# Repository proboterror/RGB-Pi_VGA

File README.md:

# RGB-Pi with VGA 15 kHz

Improved [RGB-Pi adapter](https://www.rgb-pi.com) for use with RGB-Pi OS.

Based on [open schematic published by mortaca](https://github.com/mortaca/RGB-Pi).

Original RGB-Pi documentation: [www.mortaca.com/docs/wiki](https://www.mortaca.com/docs/wiki/index.php?title=RGB-Pi)

Changes:
- Added VGA (DSUB-15) 15 kHz connector (Warning: 31 kHz VGA monitors not supported). 
- Proper sync combiner, borrowed from from [BKM-129X clone board](https://github.com/skumlos/bkm-129x-scart-vga), see also [KabukiFlux's RGBpi cable sync mixer](https://github.com/KabukiFlux/pi-rgb-cable-sync-mixer).
- Improved R-2R RGB DAC.
- PWM audio buffered with [SN74LVC2G34 Dual Buffer Gate](<datasheets/SN74LVC2G34 Dual Buffer Gate.pdf>) powered from [PS7A2033 Ultra-Low-Noise LDO](<datasheets/TPS7A20 300-mA, Ultra-Low-Noise, Low-IQ, High PSRR LDO.pdf>), with separate analog ground, in order to reduce Raspberry Pi internal power noise.
- Added 3.5 mm audio jack connector.

## Schematics:<br>

## Board view:<br>

## Bill of Materials
|Reference|Value|Footprint|Qty|
|-----|-----|-----|-----|
|C1,C2|100nF|0805|2|
|C8,C9|10uF|0805|2|
|U2|SN74LVC2G34DBVR|SOT-23-6|1|
|U3|TPS7A2033PDBVR|SOT-23-5|1|
|F1|MF-NSMF012-2| 1206 Bourns MF-NSMF012-2 0.12A 30V|1|
|J1|Raspberry_Pi_4| PinHeader_2x20_P2.54mm_Vertical |1|
|J2|SCART-F|CS-102 (SCART-21S)|1|
|J3|DE15 Socket / DSUB-15-HD / VGA| DSUB-15-HD_Socket_Horizontal P2.29x1.90mm EdgePinOffset3.03mm MountingHolesOffset4.94mm|1|
|J4|SJ1-3535NG|CUI/Same Sky Device SJ1-3535NG|1|
|Q1|MMBT3904|SOT-23|1|
|R1|120R|0805|1|
|R2,R3|1K|0805|2|
|R6|100R|0805|1|
|R7|10K|0805|1|
|R8|1K|0805|1|
|R9|470R|0805|1|
|RN1,RN2,RN5,RN8|R = 240R or 300R 1%|Resistor Array 4x0603 |4|
|RN3,RN4,RN6,RN7,RN9,RN10|2R = 475R or 604R 1%|Resistor Array 4x0603|6|

Optional (SCART 5V->12V Converter for Status & Aspect Ratio switch):

|Reference|Value|Footprint|Qty|
|-----|-----|-----|-----|
|C5|100nF|0805|1|
|C3,C4|220nF|0805|2|
|C6,C7|4.7uF|Tantalum EIA-3528-21 / Kemet-B|2|
|U1|ST662A|SO-8_3.9x4.9mm_P1.27mm|1|

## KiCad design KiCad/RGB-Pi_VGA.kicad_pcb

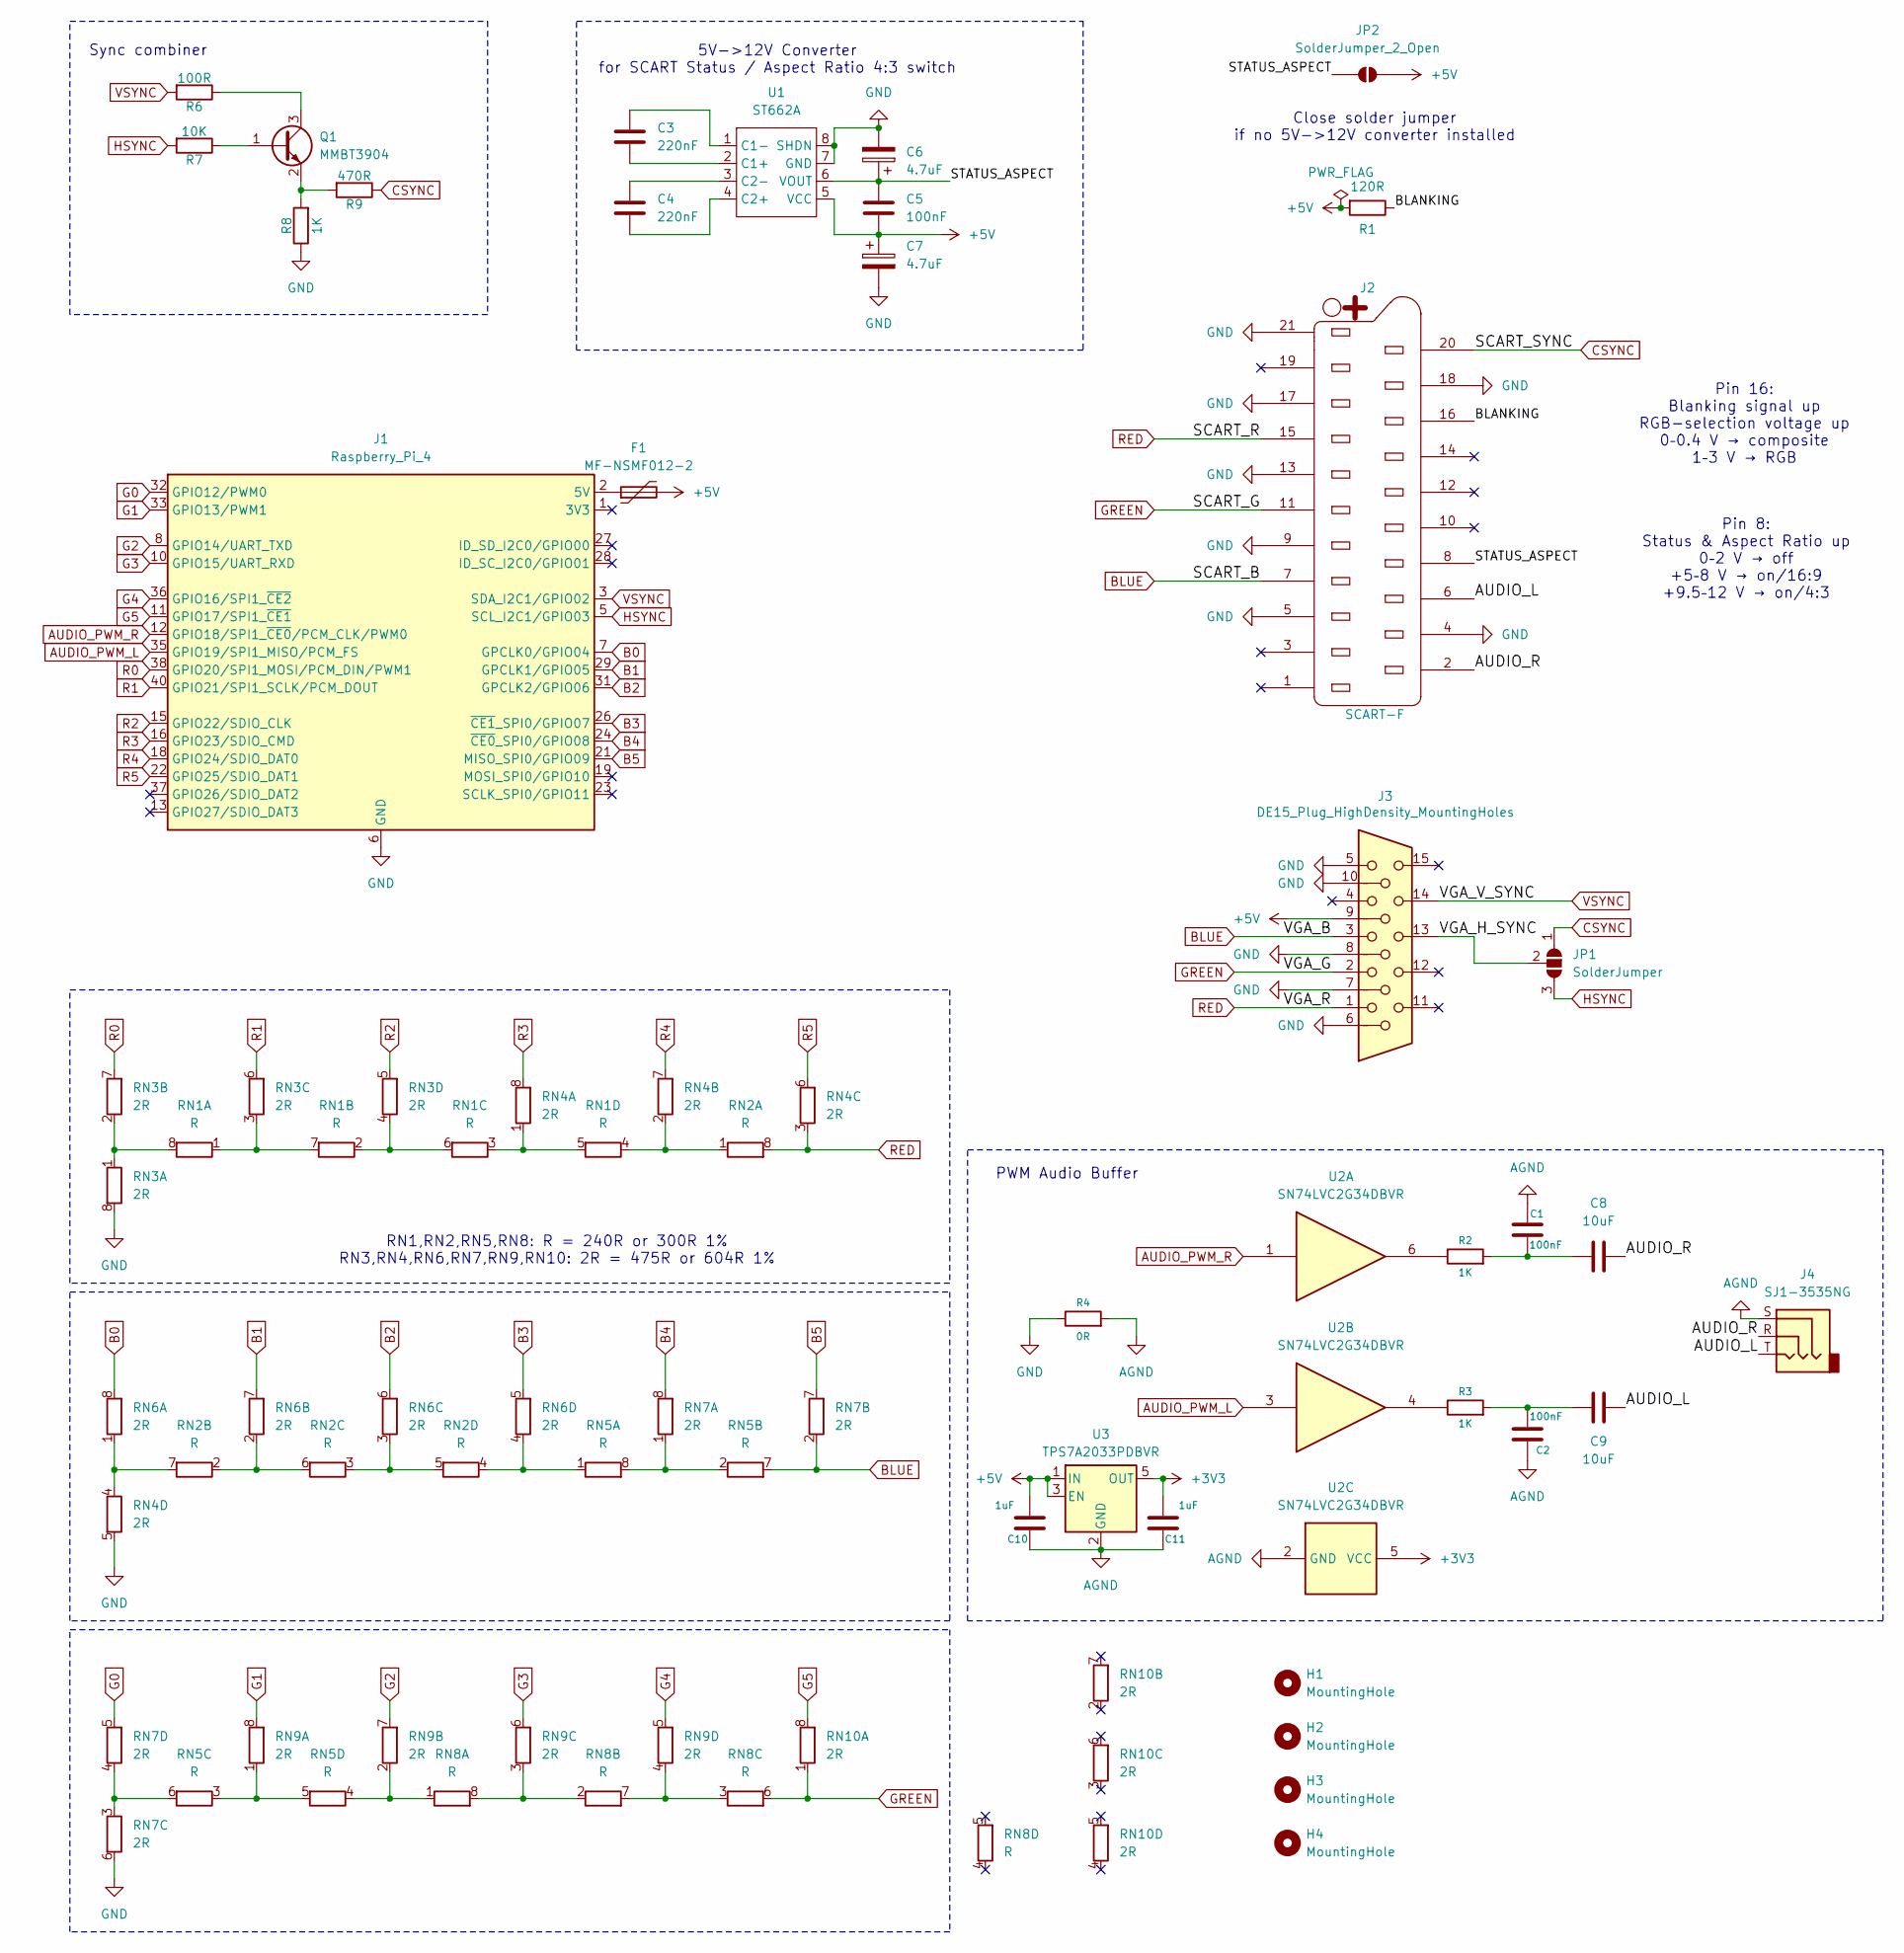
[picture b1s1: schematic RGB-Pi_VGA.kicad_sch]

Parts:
C1, C2, C5: 100nF; C_0805_2012Metric_Pad1.18x1.45mm_HandSolder
C3, C4: 220nF; C_0805_2012Metric_Pad1.18x1.45mm_HandSolder
C6, C7: 4.7uF; CP_EIA-3528-21_Kemet-B_HandSolder
C8, C9: 10uF; R_0805_2012Metric_Pad1.20x1.40mm_HandSolder
C10, C11: 1uF; C_0805_2012Metric_Pad1.18x1.45mm_HandSolder
F1: MF-NSMF012-2; Fuse_1206_3216Metric_Pad1.42x1.75mm_HandSolder
H1, H2, H3, H4: MountingHole; MountingHole_2.7mm_Pad
J1: Raspberry_Pi_4; PinHeader_2x20_P2.54mm_Vertical
J2: SCART-F; K-SCARTX-024
J3: DE15_Plug_HighDensity_MountingHoles; DSUB-15-HD_Socket_Horizontal_P2.29x1.90mm_EdgePinOffset3.03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
J4: SJ1-3535NG; Jack_3.5mm_CUI_SJ1-3535NG_Horizontal
JP1: SolderJumper; SolderJumper-3_P1.3mm_Open_RoundedPad1.0x1.5mm_NumberLabels
JP2: SolderJumper_2_Open; SolderJumper-2_P1.3mm_Open_RoundedPad1.0x1.5mm
Q1: MMBT3904; SOT-23
R1: 120R; R_0805_2012Metric_Pad1.20x1.40mm_HandSolder
R2, R3, R8: 1K; R_0805_2012Metric_Pad1.20x1.40mm_HandSolder
R4: 0R; R_0805_2012Metric_Pad1.20x1.40mm_HandSolder
R6: 100R; R_0805_2012Metric_Pad1.20x1.40mm_HandSolder
R7: 10K; R_0805_2012Metric_Pad1.20x1.40mm_HandSolder
R9: 470R; R_0805_2012Metric_Pad1.20x1.40mm_HandSolder
RN1, RN2, RN5, RN8: R; R_Array_Convex_4x0603
RN3, RN4, RN6, RN7, RN9, RN10: 2R; R_Array_Convex_4x0603
U1: ST662A; SO-8_3.9x4.9mm_P1.27mm
U2: SN74LVC2G34DBVR; SOT-23-6_Handsoldering
U3: TPS7A2033PDBVR; SOT-23-5

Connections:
+3V3: C11.2, U2.5 (VCC), U3.5 (OUT)
+5V: C5.2, C7.1, C10.2, F1.2, J3.9, JP2.2 (B), R1.2, U1.5 (VCC), U3.1 (IN), U3.3 (EN)
/AUDIO_L: C9.2, J2.6, J4.T
/AUDIO_R: C8.2, J2.2, J4.R
/BLANKING: J2.16, R1.1
/STATUS_ASPECT: C5.1, C6.1, J2.8, JP2.1 (A), U1.6 (VOUT)
/VGA_H_SYNC: J3.13, JP1.2 (C)
AGND: C1.1, C2.1, C10.1, C11.1, J4.S, R4.2, U2.2 (GND), U3.2 (GND)
AUDIO_PWM_L: J1.35 (GPIO19/SPI1_MISO/PCM_FS), U2.3
AUDIO_PWM_R: J1.12 (GPIO18/SPI1_~CE0/PCM_CLK/PWM0), U2.1
B0: J1.7 (GPCLK0/GPIO04), RN6.8 (R1.2)
B1: J1.29 (GPCLK1/GPIO05), RN6.7 (R2.2)
B2: J1.31 (GPCLK2/GPIO06), RN6.6 (R3.2)
B3: J1.26 (~CE1_SPI0/GPIO07), RN6.5 (R4.2)
B4: J1.24 (~CE0_SPI0/GPIO08), RN7.8 (R1.2)
B5: J1.21 (MISO_SPI0/GPIO09), RN7.7 (R2.2)
BLUE: J2.7, J3.3, RN5.7 (R2.2), RN7.2 (R2.1)
CSYNC: J2.20, JP1.1 (A), R9.1
G0: J1.32 (GPIO12/PWM0), RN7.5 (R4.2)
G1: J1.33 (GPIO13/PWM1), RN9.8 (R1.2)
G2: J1.8 (GPIO14/UART_TXD), RN9.7 (R2.2)
G3: J1.10 (GPIO15/UART_RXD), RN9.6 (R3.2)
G4: J1.36 (GPIO16/SPI1_~CE2), RN9.5 (R4.2)
G5: J1.11 (GPIO17/SPI1_~CE1), RN10.8 (R1.2)
GND: C6.2, C7.2, J1.6 (GND), J1.9 (GND), J1.14 (GND), J1.20 (GND), J1.25 (GND), J1.30 (GND), J1.34 (GND), J1.39 (GND), J2.4, J2.5, J2.9, J2.13, J2.17, J2.18, J2.21, J3.5, J3.6, J3.7, J3.8, J3.10, R4.1, R8.1, RN3.8 (R1.2), RN4.5 (R4.2), RN7.6 (R3.2), U1.7 (GND), U1.8 (SHDN)
GREEN: J2.11, J3.2, RN8.6 (R3.2), RN10.1 (R1.1)
HSYNC: J1.5 (SCL_I2C1/GPIO03), JP1.3 (B), R7.2
unnamed: C1.2, C8.1, R2.2
unnamed: C2.2, C9.1, R3.2
unnamed: F1.1, J1.2 (5V), J1.4 (5V)
unnamed: Q1.1 (B), R7.1
unnamed: Q1.3 (C), R6.1
unnamed: Q1.2 (E), R8.2, R9.2
unnamed: R2.1, U2.6
unnamed: R3.1, U2.4
unnamed: RN1.1 (R1.1), RN1.7 (R2.2), RN3.3 (R3.1)
unnamed: RN1.8 (R1.2), RN3.1 (R1.1), RN3.2 (R2.1)
unnamed: RN1.2 (R2.1), RN1.6 (R3.2), RN3.4 (R4.1)
unnamed: RN1.3 (R3.1), RN1.5 (R4.2), RN4.1 (R1.1)
unnamed: RN1.4 (R4.1), RN2.1 (R1.1), RN4.2 (R2.1)
unnamed: RN2.2 (R2.1), RN2.6 (R3.2), RN6.2 (R2.1)
unnamed: RN2.7 (R2.2), RN4.4 (R4.1), RN6.1 (R1.1)
unnamed: RN2.3 (R3.1), RN2.5 (R4.2), RN6.3 (R3.1)
unnamed: RN2.4 (R4.1), RN5.1 (R1.1), RN6.4 (R4.1)
unnamed: RN5.2 (R2.1), RN5.8 (R1.2), RN7.1 (R1.1)
unnamed: RN5.3 (R3.1), RN5.5 (R4.2), RN9.1 (R1.1)
unnamed: RN5.6 (R3.2), RN7.3 (R3.1), RN7.4 (R4.1)
unnamed: RN5.4 (R4.1), RN8.1 (R1.1), RN9.2 (R2.1)
unnamed: RN8.2 (R2.1), RN8.8 (R1.2), RN9.3 (R3.1)
unnamed: RN8.3 (R3.1), RN8.7 (R2.2), RN9.4 (R4.1)
unnamed: C3.2, U1.2 (C1+)
unnamed: C3.1, U1.1 (C1-)
unnamed: C4.2, U1.4 (C2+)
unnamed: C4.1, U1.3 (C2-)
R0: J1.38 (GPIO20/SPI1_MOSI/PCM_DIN/PWM1), RN3.7 (R2.2)
R1: J1.40 (GPIO21/SPI1_SCLK/PCM_DOUT), RN3.6 (R3.2)
R2: J1.15 (GPIO22/SDIO_CLK), RN3.5 (R4.2)
R3: J1.16 (GPIO23/SDIO_CMD), RN4.8 (R1.2)
R4: J1.18 (GPIO24/SDIO_DAT0), RN4.7 (R2.2)
R5: J1.22 (GPIO25/SDIO_DAT1), RN4.6 (R3.2)
RED: J2.15, J3.1, RN2.8 (R1.2), RN4.3 (R3.1)
VSYNC: J1.3 (SDA_I2C1/GPIO02), J3.14, R6.2

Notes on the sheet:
5V->12V Converter for SCART Status / Aspect Ratio 4:3 switch
PWM Audio Buffer
RN1,RN2,RN5,RN8: R = 240R or 300R 1% RN3,RN4,RN6,RN7,RN9,RN10: 2R = 475R or 604R 1%
Pin 16: Blanking signal up RGB-selection voltage up 0–0.4 V → composite 1–3 V → RGB
Sync combiner
Close solder jumper if no 5V->12V converter installed
Pin 8: Status & Aspect Ratio up 0–2 V → off +5–8 V → on/16:9 +9.5–12 V → on/4:3

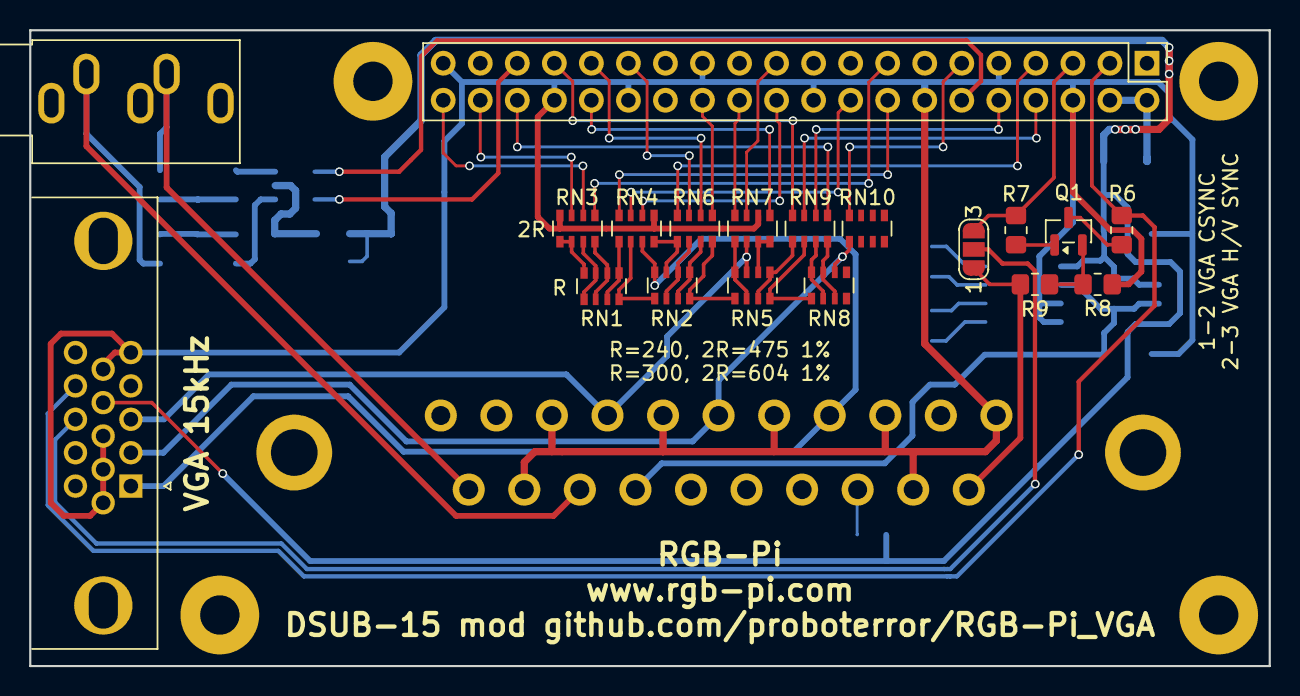
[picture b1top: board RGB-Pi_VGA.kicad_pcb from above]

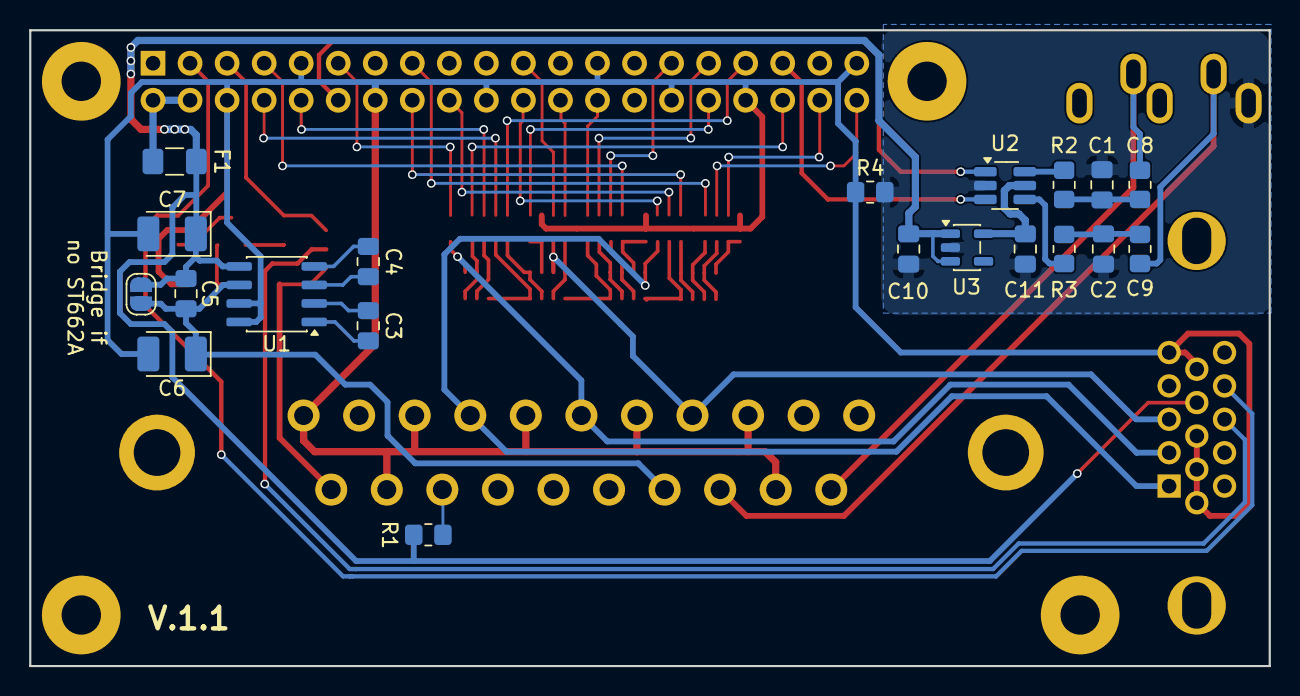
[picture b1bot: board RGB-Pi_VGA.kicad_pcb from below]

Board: 2 copper layers, 85.0 x 43.6 mm, 44 parts (20 on the bottom side), 62 nets.

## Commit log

2026-05-02 Initial implementation.
2026-05-02 Update README.md.
2026-05-02 Add +5V PWR_FLAG to schematic.
2026-05-02 Add PCB dimension.
2026-05-02 Change C8, C9 footprints from 1206 to 0805.
2026-05-02 Update svg schematic dimensions.
2026-05-27 Correct DE15/VGA connector pinout.
2026-05-27 Update PCB matching schematic.
2026-06-13 Board version 1.1. Correct VGA connector pinout. PWM audio buffered with SN74LVC2G34 Dual Buffer Gate, powered from PS7A2033 Ultra-Low-Noise LDO, with separate analog ground, in order to reduce Raspb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
